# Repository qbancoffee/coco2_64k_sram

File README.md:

# coco2_64k_sram
Static RAM board for the Tandy Color Computer 2 model 26-3134

This KiCAD project includes the schematic and PCB design for a 64k static RAM board for the
Tandy Color Computer 2 model 26-3134. It is designed to plug into the expansion port.
There are two versions of the board in this repo, the main one which is the SMD version
and there is a through hole version under "coco2_3134_64k_static_ram_board_tht".

## Credits
The design for this board was inspired by the following.
- [Ciaran Ascomb's 512K static RAM board for the CoCo 3.](https://gitlab.com/sixxie/cc3-512k)
- [Jamaru's static RAM board for for the Commodore 64, based on Garrit4's design](https://github.com/jamarju/c64-sram)
- [Garrit4's SRAM board design.](https://www.lemon64.com/forum/viewtopic.php?p=773935#773935)

## Docs
- [Schematic](https://github.com/qbancoffee/coco2_64k_sram/blob/main/pdfs/schematic.pdf)
- [Rendered Image top](https://github.com/qbancoffee/coco2_64k_sram/blob/main/images/board_top_rendered.png)
- [Rendered Image bottom](https://github.com/qbancoffee/coco2_64k_sram/blob/main/images/board_bottom_rendered.png)
- [Board top](https://github.com/qbancoffee/coco2_64k_sram/blob/main/images/board_top.jpg)
- [Board bottom](https://github.com/qbancoffee/coco2_64k_sram/blob/main/images/board_bottom.jpg)
- [Board installed](https://github.com/qbancoffee/coco2_64k_sram/blob/main/images/board_installed.jpg)
- [Interactive BOM](https://htmlpreview.github.io/?https://github.com/qbancoffee/coco2_64k_sram/blob/main/bom/ibom.html)
- [Interactive BOM for the through hole version](https://htmlpreview.github.io/?https://github.com/qbancoffee/coco2_64k_sram/blob/main/bom/ibom_tht.html)
- [Bill Of Materials (BOM)](https://github.com/qbancoffee/coco2_64k_sram/blob/main/bom/bom.csv)
- [Bill Of Materials for the through hole version (BOM)](https://github.com/qbancoffee/coco2_64k_sram/blob/main/bom/bom_tht.csv)

## Videos
- [Installing the board in a CoCo 2](https://youtu.be/qNmRELRTp34)
- [Making a through hole version of the board](https://youtu.be/qkUWCKWGy-E)

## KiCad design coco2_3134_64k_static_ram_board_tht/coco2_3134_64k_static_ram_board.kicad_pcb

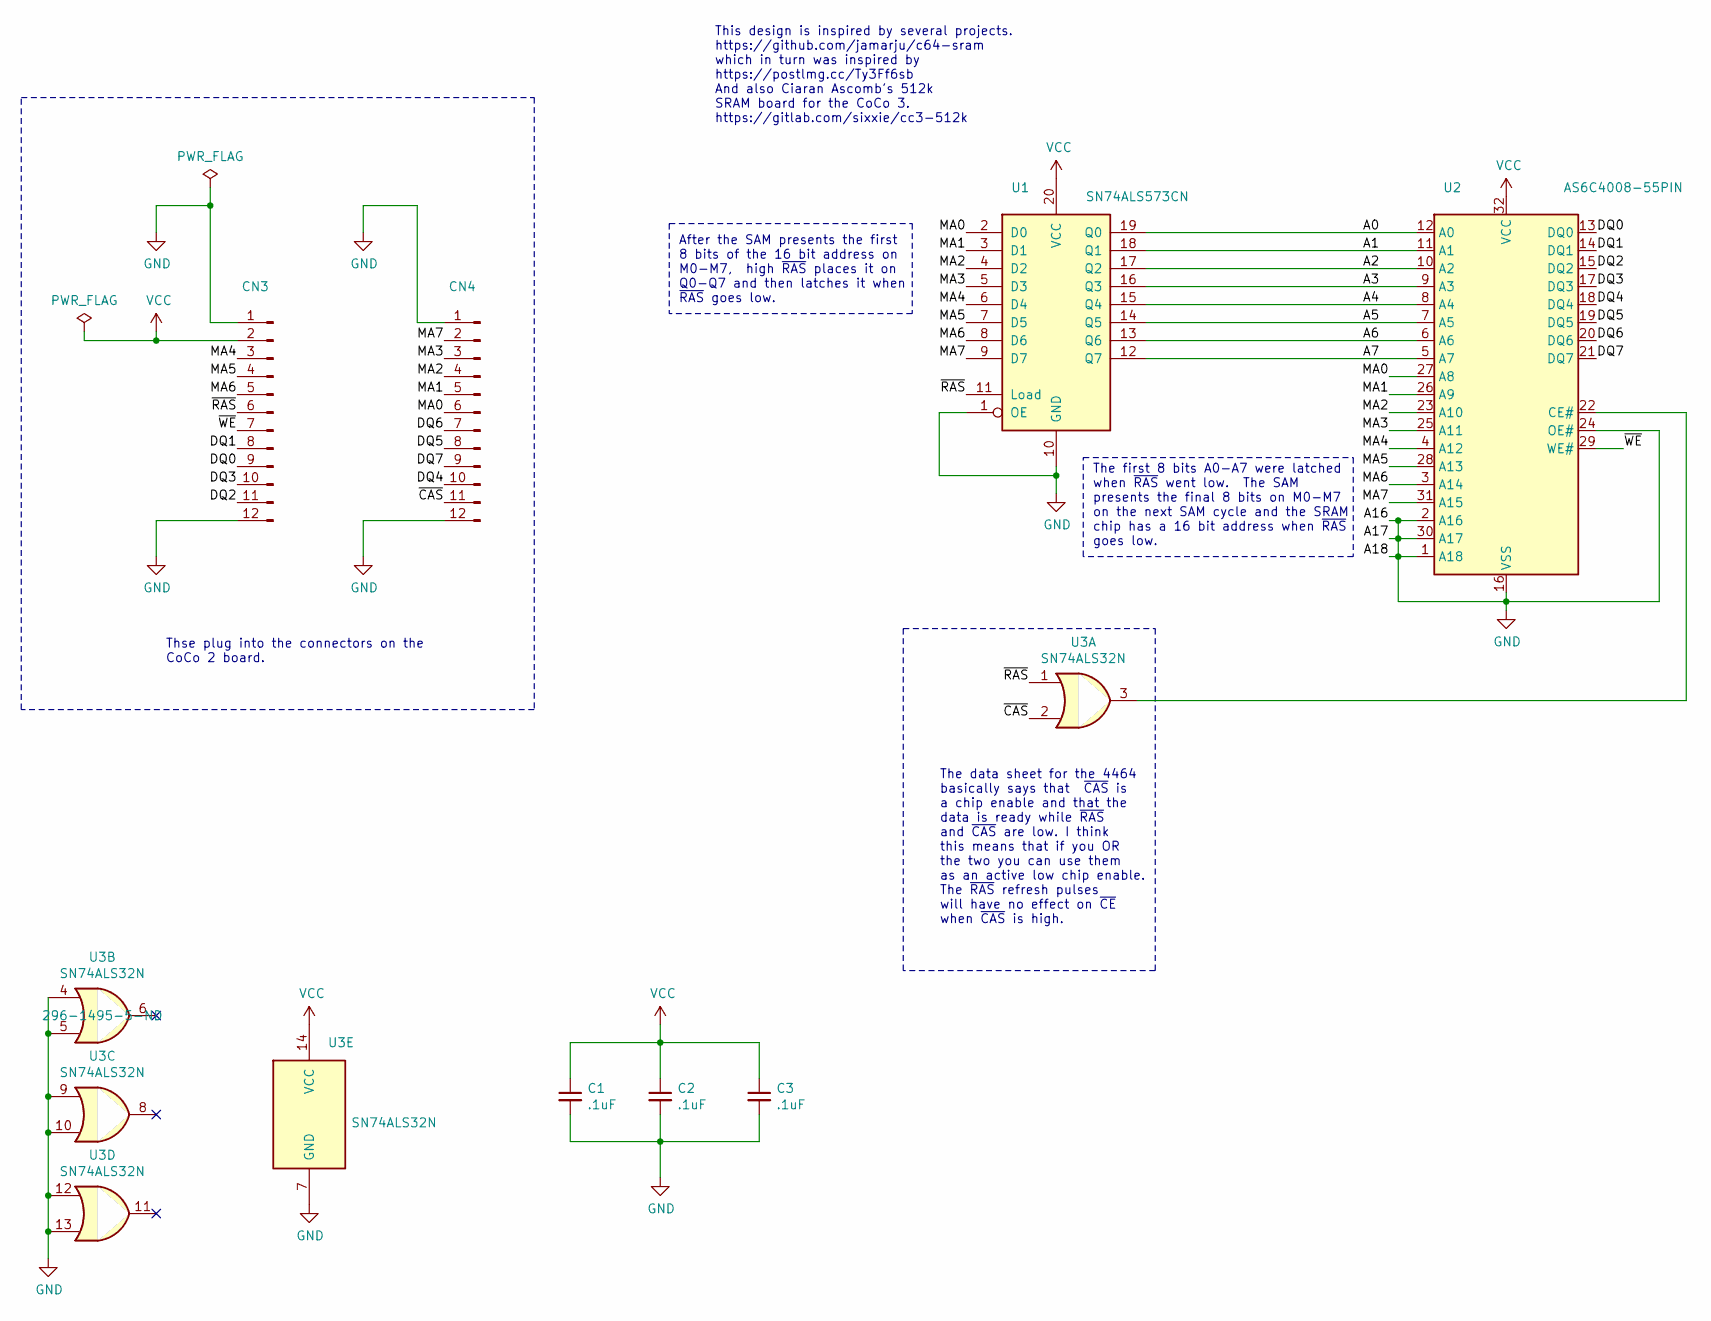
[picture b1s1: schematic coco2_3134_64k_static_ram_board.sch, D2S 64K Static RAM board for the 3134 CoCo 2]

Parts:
C1, C2, C3: .1uF; C_Disc_D4.7mm_W2.5mm_P5.00mm; manufacturer part# RDER71H104K0K1H03B
CN3, CN4: Conn_01x12_Male; PinHeader_1x12_P2.54mm_Vertical
U1: SN74ALS573CN; DIP-20_W7.62mm_Socket_LongPads; manufacturer part# SN74ALS573CN
U2: AS6C4008-55PIN; DIP-32_W15.24mm; manufacturer part# AS6C4008-55PIN
U3: SN74ALS32N; DIP-14_W7.62mm_Socket_LongPads; manufacturer part# SN74ALS32N

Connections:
/A0: U1.19 (Q0), U2.12 (A0)
/A1: U1.18 (Q1), U2.11 (A1)
/A2: U1.17 (Q2), U2.10 (A2)
/A3: U1.16 (Q3), U2.9 (A3)
/A4: U1.15 (Q4), U2.8 (A4)
/A5: U1.14 (Q5), U2.7 (A5)
/A6: U1.13 (Q6), U2.6 (A6)
/A7: U1.12 (Q7), U2.5 (A7)
/DQ0: CN3.9, U2.13 (DQ0)
/DQ1: CN3.8, U2.14 (DQ1)
/DQ2: CN3.11, U2.15 (DQ2)
/DQ3: CN3.10, U2.17 (DQ3)
/DQ4: CN4.10, U2.18 (DQ4)
/DQ5: CN4.8, U2.19 (DQ5)
/DQ6: CN4.7, U2.20 (DQ6)
/DQ7: CN4.9, U2.21 (DQ7)
/MA0: CN4.6, U1.2 (D0), U2.27 (A8)
/MA1: CN4.5, U1.3 (D1), U2.26 (A9)
/MA2: CN4.4, U1.4 (D2), U2.23 (A10)
/MA3: CN4.3, U1.5 (D3), U2.25 (A11)
/MA4: CN3.3, U1.6 (D4), U2.4 (A12)
/MA5: CN3.4, U1.7 (D5), U2.28 (A13)
/MA6: CN3.5, U1.8 (D6), U2.3 (A14)
/MA7: CN4.2, U1.9 (D7), U2.31 (A15)
/~CAS: CN4.11, U3.2
/~RAS: CN3.6, U1.11 (Load), U3.1
/~WE: CN3.7, U2.29 (WE#)
GND: C1.2, C2.2, C3.2, CN3.1, CN3.12, CN4.1, CN4.12, U1.1 (OE), U1.10 (GND), U2.1 (A18), U2.2 (A16), U2.16 (VSS), U2.24 (OE#), U2.30 (A17), U3.4, U3.5, U3.7 (GND), U3.9, U3.10, U3.12, U3.13
unnamed: U2.22 (CE#), U3.3
VCC: C1.1, C2.1, C3.1, CN3.2, U1.20 (VCC), U2.32 (VCC), U3.14 (VCC)

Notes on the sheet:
The data sheet for the 4464 basically says that ~CAS~ is a chip enable and that the data is ready while ~RAS~ and ~CAS~ are low. I think this means that if you OR the two you can use them as an active low chip enable. The ~RAS~ refresh pulses will have no effect on ~CE~ when ~CAS~ is high.
This design is inspired by several projects. https://github.com/jamarju/c64-sram which in turn was inspired by https://postlmg.cc/Ty3Ff6sb And also Ciaran Ascomb's 512k SRAM board for the CoCo 3. https://gitlab.com/sixxie/cc3-512k
Thse plug into the connectors on the CoCo 2 board.
After the SAM presents the first 8 bits of the 16 bit address on M0-M7, high ~RAS~ places it on Q0-Q7 and then latches it when ~RAS~ goes low.
The first 8 bits A0-A7 were latched when ~RAS~ went low. The SAM presents the final 8 bits on M0-M7 on the next SAM cycle and the SRAM chip has a 16 bit address when ~RAS~ goes low.

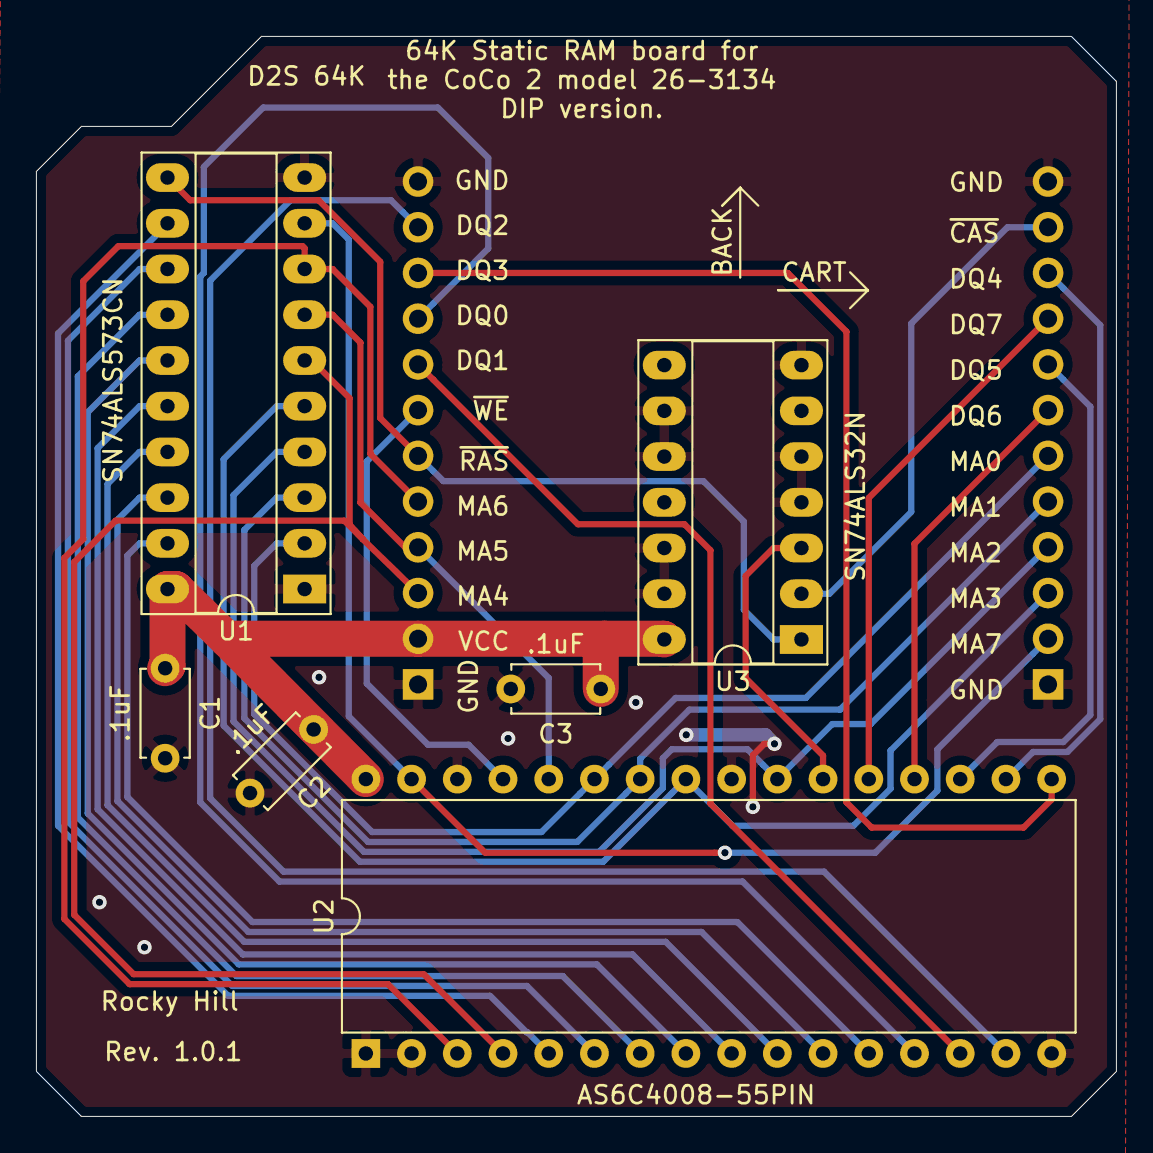
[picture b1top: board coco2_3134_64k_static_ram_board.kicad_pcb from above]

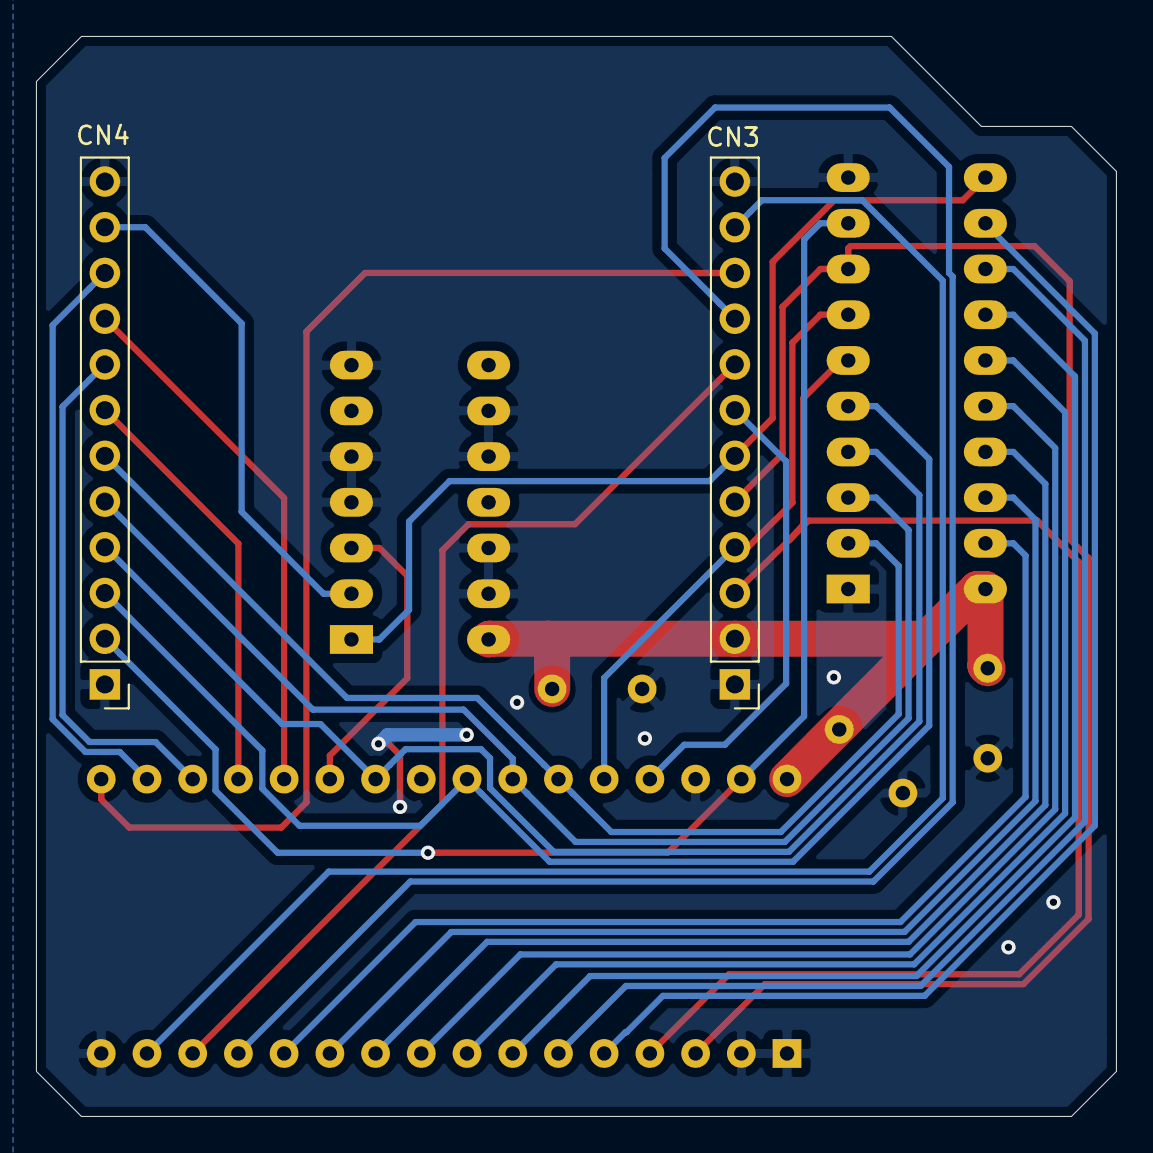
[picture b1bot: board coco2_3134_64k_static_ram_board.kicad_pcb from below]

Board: 2 copper layers, 60.0 x 60.0 mm, 8 parts (2 on the bottom side), 30 nets.

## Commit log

2022-08-01 added images and BOM
2022-08-01 added missing part number
2022-08-09 made corrections to descriptions on how the address is converted for use with the SRAM chip
2022-09-12 added through hole version of the board.
